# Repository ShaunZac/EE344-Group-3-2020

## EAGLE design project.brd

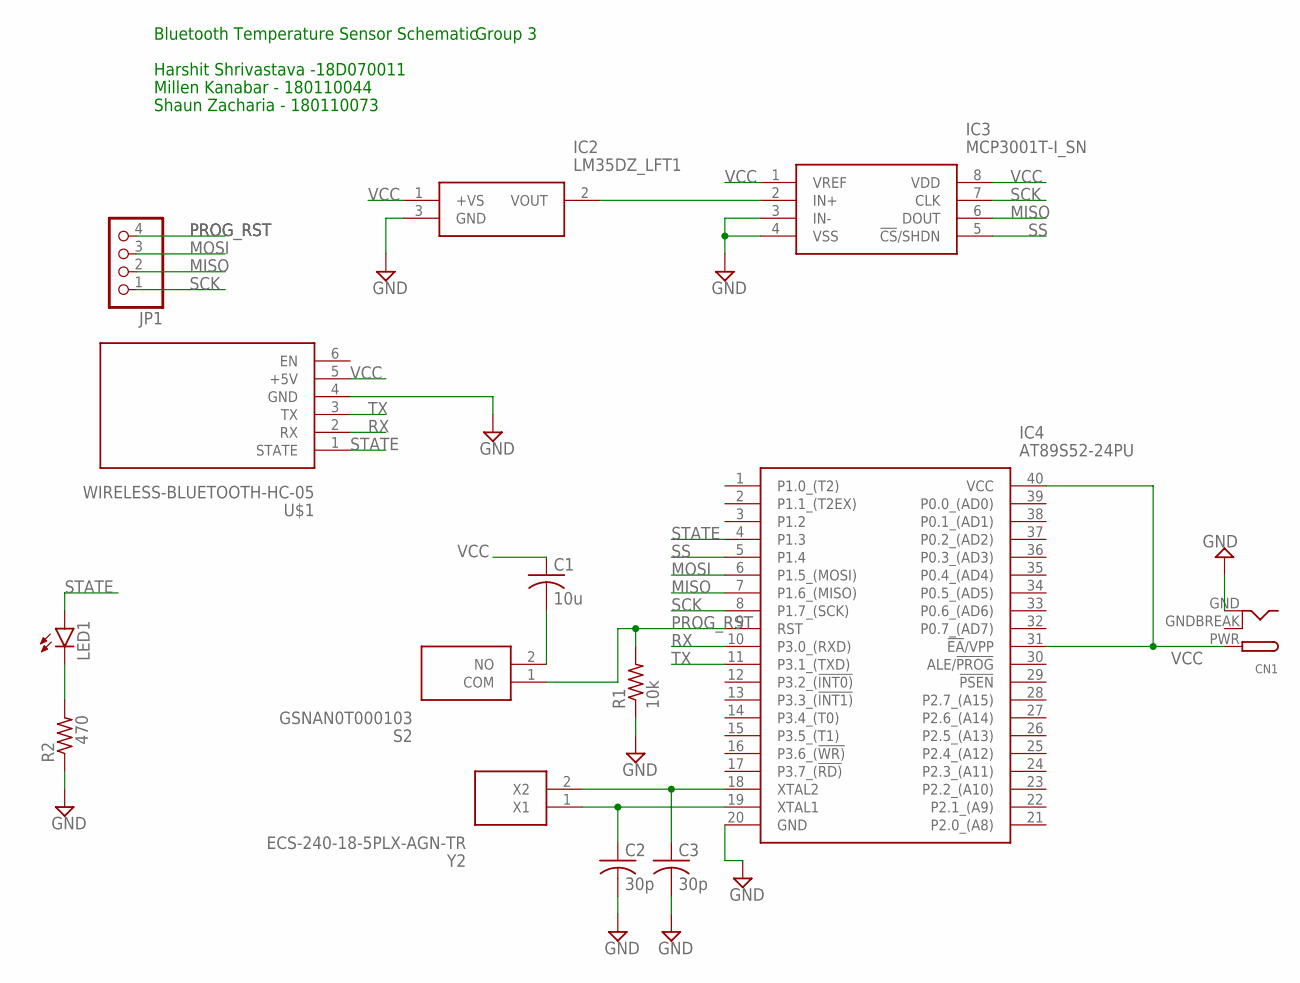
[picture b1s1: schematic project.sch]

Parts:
C1: 10u; C025-050X050
C2, C3: 30p; C025-050X050
CN1: DCBARRELPTH; DCJACK_2MM_PTH
IC2: LM35DZ_LFT1; LP0003A
IC3: MCP3001T-I_SN; SOIC127P600X175-8N
IC4: AT89S52-24PU; DIP1556W56P254L5232H483Q40N
JP1: PINHD-1X4; 1X04
LED1: LED; SMARTLED-TTW
R1: 10k; 0207/10
R2: 470; 0207/10
S2: GSNAN0T000103
U$1: WIRELESS-BLUETOOTH-HC-05
Y2: ECS-240-18-5PLX-AGN-TR; ECS240185PLXAGNTR

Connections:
GND: C2.2, C3.2, CN1.GND, IC2.3 (GND), IC3.3 (IN-), IC3.4 (VSS), IC4.20 (GND), R1.1, R2.1, U$1.4 (GND)
GNDBREAK: CN1.GNDBREAK
MISO: IC3.6 (DOUT), IC4.7 (P1.6_(MISO)), JP1.2
MOSI: IC4.6 (P1.5_(MOSI)), JP1.3
unnamed: C3.1, IC4.18 (XTAL2), Y2.2 (X2)
unnamed: C2.1, IC4.19 (XTAL1), Y2.1 (X1)
unnamed: IC2.2 (VOUT), IC3.2 (IN+)
unnamed: C1.2, S2.2 (NO)
unnamed: LED1.C@1 (C), R2.2
PROG_RST: IC4.9 (RST), JP1.4, R1.2, S2.1 (COM)
RX: IC4.10 (P3.0_(RXD)), U$1.2 (RX)
SCK: IC3.7 (CLK), IC4.8 (P1.7_(SCK)), JP1.1
SS: IC3.5 (!CS!/SHDN), IC4.5 (P1.4)
STATE: IC4.4 (P1.3), LED1.A@1 (A), U$1.1 (STATE)
TX: IC4.11 (P3.1_(TXD)), U$1.3 (TX)
VCC: C1.1, CN1.PWR, IC2.1 (+VS), IC3.1 (VREF), IC3.8 (VDD), IC4.31 (!EA!/VPP), IC4.40 (VCC), U$1.5 (+5V)

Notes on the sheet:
Bluetooth Temperature Sensor Schematic
Harshit Shrivastava -18D070011
Millen Kanabar - 180110044
Shaun Zacharia - 180110073
Group 3

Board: 2 copper layers, 14 parts (0 on the bottom side), 15 nets, no tracks yet.

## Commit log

2021-04-04 Add Report 1
2021-04-15 Update the schematic

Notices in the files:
parts and their libraries:
HC-05: Released under the Creative Commons Attribution 4.0 International License: http://creativecommons.org/licenses/by/4.0
